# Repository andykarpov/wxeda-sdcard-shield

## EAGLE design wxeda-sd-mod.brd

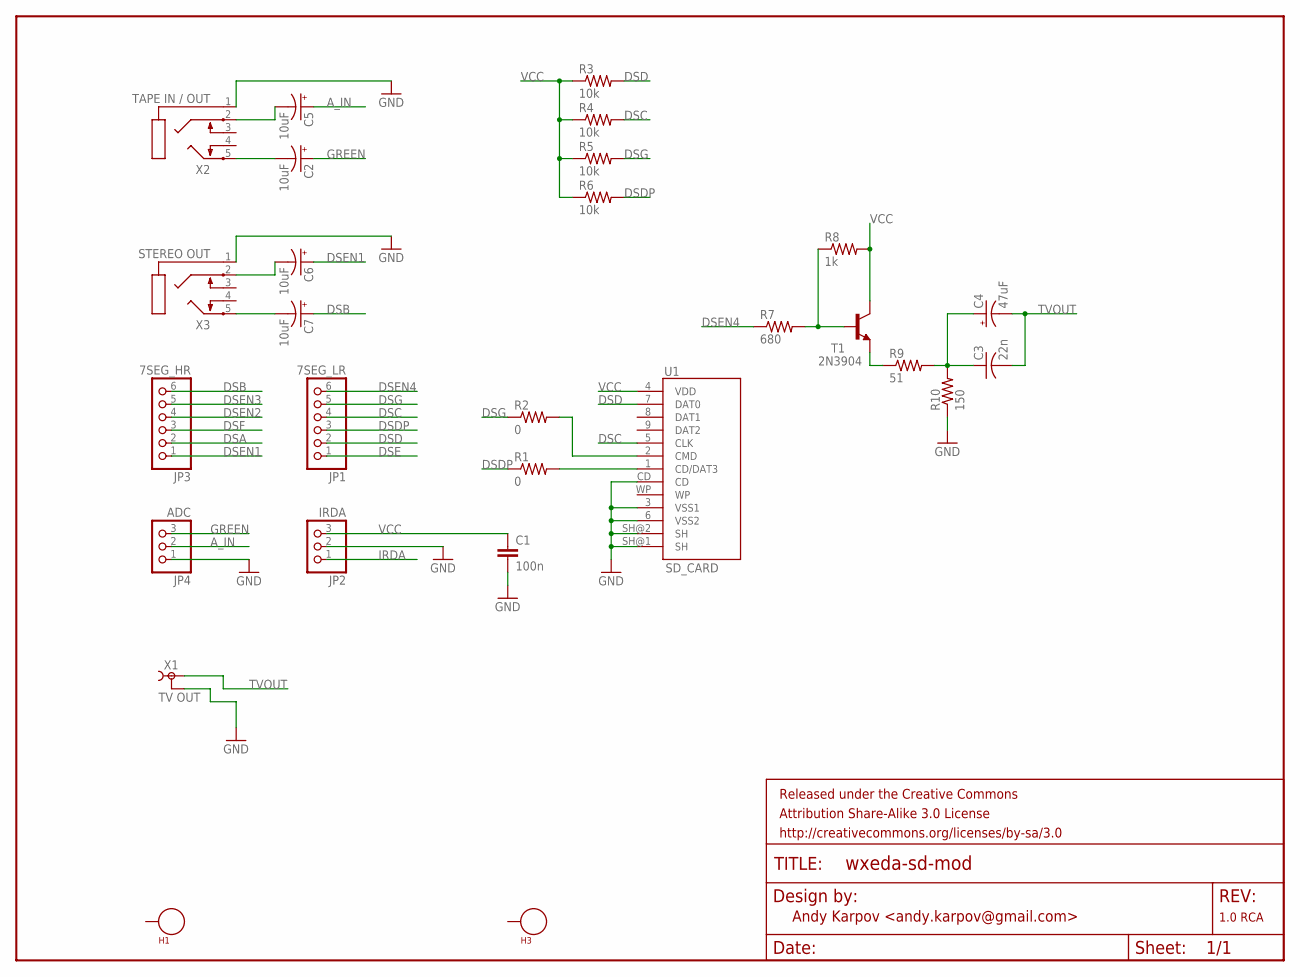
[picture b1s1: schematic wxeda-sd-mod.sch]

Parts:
C1: 100n; 1206
C2, C5, C6, C7: 10uF; E2,5-6E
C3: 22n; C050-025X075
C4: 47uF; E2,5-6E
FRAME1: FRAME-LETTER; CREATIVE_COMMONS
H1, H3: SEW_HOLE; SIMPLE_HOLE
JP1: 7SEG_LR; 1X06
JP2: IRDA; 1X03
JP3: 7SEG_HR; 1X06
JP4: ADC; 1X03
R1, R2: 0; AXIAL-0.3
R3, R4, R5, R6: 10k; AXIAL-0.3
R7: 680; AXIAL-0.3
R8: 1k; AXIAL-0.3
R9: 51; AXIAL-0.3
R10: 150; AXIAL-0.3
T1: 2N3904; TO92
U1: SD_CARD; SDCARD_4UCONN
X1: TV OUT; TOBU3
X2: TAPE IN / OUT; STX3100
X3: STEREO OUT; STX3100

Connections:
A_IN: C5.+, JP4.2
DSA: JP3.2
DSB: C7.+, JP3.6
DSC: JP1.4, R4.P$2 (2), U1.5 (CLK)
DSD: JP1.2, R3.P$2 (2), U1.7 (DAT0)
DSDP: JP1.3, R1.P$1 (1), R6.P$2 (2)
DSE: JP1.1
DSEN1: C6.+, JP3.1
DSEN2: JP3.4
DSEN3: JP3.5
DSEN4: JP1.6, R7.P$1 (1)
DSF: JP3.3
DSG: JP1.5, R2.P$1 (1), R5.P$2 (2)
GND: C1.2, JP2.2, JP4.1, R10.P$1 (1), U1.3 (VSS1), U1.6 (VSS2), U1.CD, U1.SH@1 (SH), U1.SH@2 (SH), X1.2, X1.2@1 (2), X1.2@2 (2), X2.1, X3.1
GREEN: C2.+, JP4.3
IRDA: JP2.1
unnamed: R1.P$2 (2), U1.1 (CD/DAT3)
unnamed: R7.P$2 (2), R8.P$1 (1), T1.2 (B)
unnamed: R2.P$2 (2), U1.2 (CMD)
unnamed: C2.-, X2.5
unnamed: C5.-, X2.2
unnamed: R9.P$1 (1), T1.3 (E)
unnamed: C3.1, C4.+, R9.P$2 (2), R10.P$2 (2)
unnamed: C6.-, X3.2
unnamed: C7.-, X3.5
TVOUT: C3.2, C4.-, X1.1
VCC: C1.1, JP2.3, R3.P$1 (1), R4.P$1 (1), R5.P$1 (1), R6.P$1 (1), R8.P$2 (2), T1.1 (C), U1.4 (VDD)

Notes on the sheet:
Andy Karpov <andy.karpov@gmail.com>
1.0 RCA

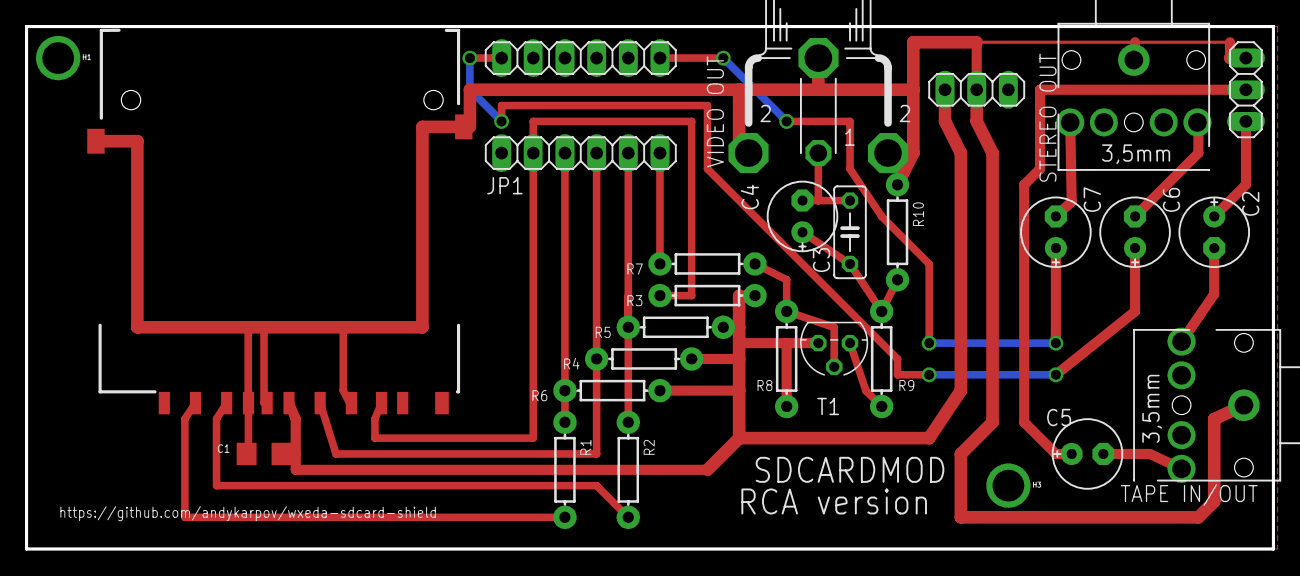
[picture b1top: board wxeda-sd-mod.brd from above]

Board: 2 copper layers, 100.0 x 41.9 mm, 29 parts (0 on the bottom side), 21 nets.

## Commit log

2014-09-11 Added schematic and pcb design screenshots
2014-09-11 Added pull-up resistors
2014-09-13 Added tape in/out and tv out
2014-09-13 small improvements
2014-09-14 minor changes
2014-09-14 Added S-Video connector against RCA
2014-09-14 hotfixes, added external library for minidin4 connector
2014-09-14 release
2014-09-14 Added stereo output
2014-09-14 Added stereo out
2014-09-14 Added simplified version
2014-09-18 final RCA version

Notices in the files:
parts and their libraries:
SparkFun-Connectors: Licensing: CC v3.0 Share-Alike You are welcome to use this library for commercial purposes.
SparkFun-Aesthetics: Released under the Creative Commons Attribution Share-Alike 3.0 License
SparkFun-Aesthetics: http://creativecommons.org/licenses/by-sa/3.0
